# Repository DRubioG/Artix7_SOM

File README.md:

# Artix7_SOM
 This a SOM board of an Artix 7

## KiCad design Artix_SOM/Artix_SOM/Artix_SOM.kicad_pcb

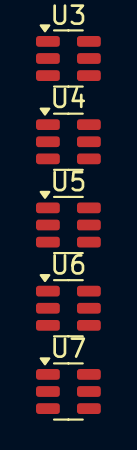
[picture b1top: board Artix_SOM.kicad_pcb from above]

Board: 2 copper layers, 5 parts (0 on the bottom side), 2 nets, no tracks yet.

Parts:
U3, U4, U5, U6, U7: TPS563200; SOT-23-6

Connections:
+5V: U3.3 (VIN), U4.3 (VIN), U5.3 (VIN), U6.3 (VIN), U7.3 (VIN)
GND: U3.1 (GND), U4.1 (GND), U5.1 (GND), U6.1 (GND), U7.1 (GND)

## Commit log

2024-10-15 update dc source
